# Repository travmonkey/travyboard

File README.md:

# travyboard

## A corne style keyboard with the Pico SDK and TinyUSB

A personal project demonstrating how to build a keyboard using the 
Raspberry Pi Pico microcontroller in c++.

### Requirements

- Two Raspberry Pi Picos
- Cmake and gcc/g++ installed. May want to set up wsl2 on Windows.
- Pico SDK [GitHub Repo](https://github.com/raspberrypi/pico-sdk)

### Setup

1. Clone the Pico SDK and update the submodules
```sh
git clone https://github.com/raspberrypi/pico-sdk.git
cd pico-sdk
git submodule update --init
```

2. Set an environment variable so cmake can find the sdk
```sh
export PICO_SDK_PATH=`<pico sdk path>`
```

3. Clone this repository:
```sh
git clone https://github.com/travmonkey/travyboard.git
cd travyboard
```

4. Create build folder and build the project:
```sh
cd firmware
mkdir build && cd build
cmake -DCMAKE_EXPORT_COMPILE_COMMANDS=ON .. # Export the compile commands for clangd to see
make
```

5. Mount and flash both picos with the master and slave compiled .uf2 code.
```sh
mkdir ~/rpi-pico
sudo fdisk -l # Find the pico device
sudo mount /dev/sdx1 /home/`<user>`/rpi-pico
sudo cp src/master.uf2 /home/`<user>`/rpi-pico/
```
Alternativly you can modify the script I wrote to include your own directories and username

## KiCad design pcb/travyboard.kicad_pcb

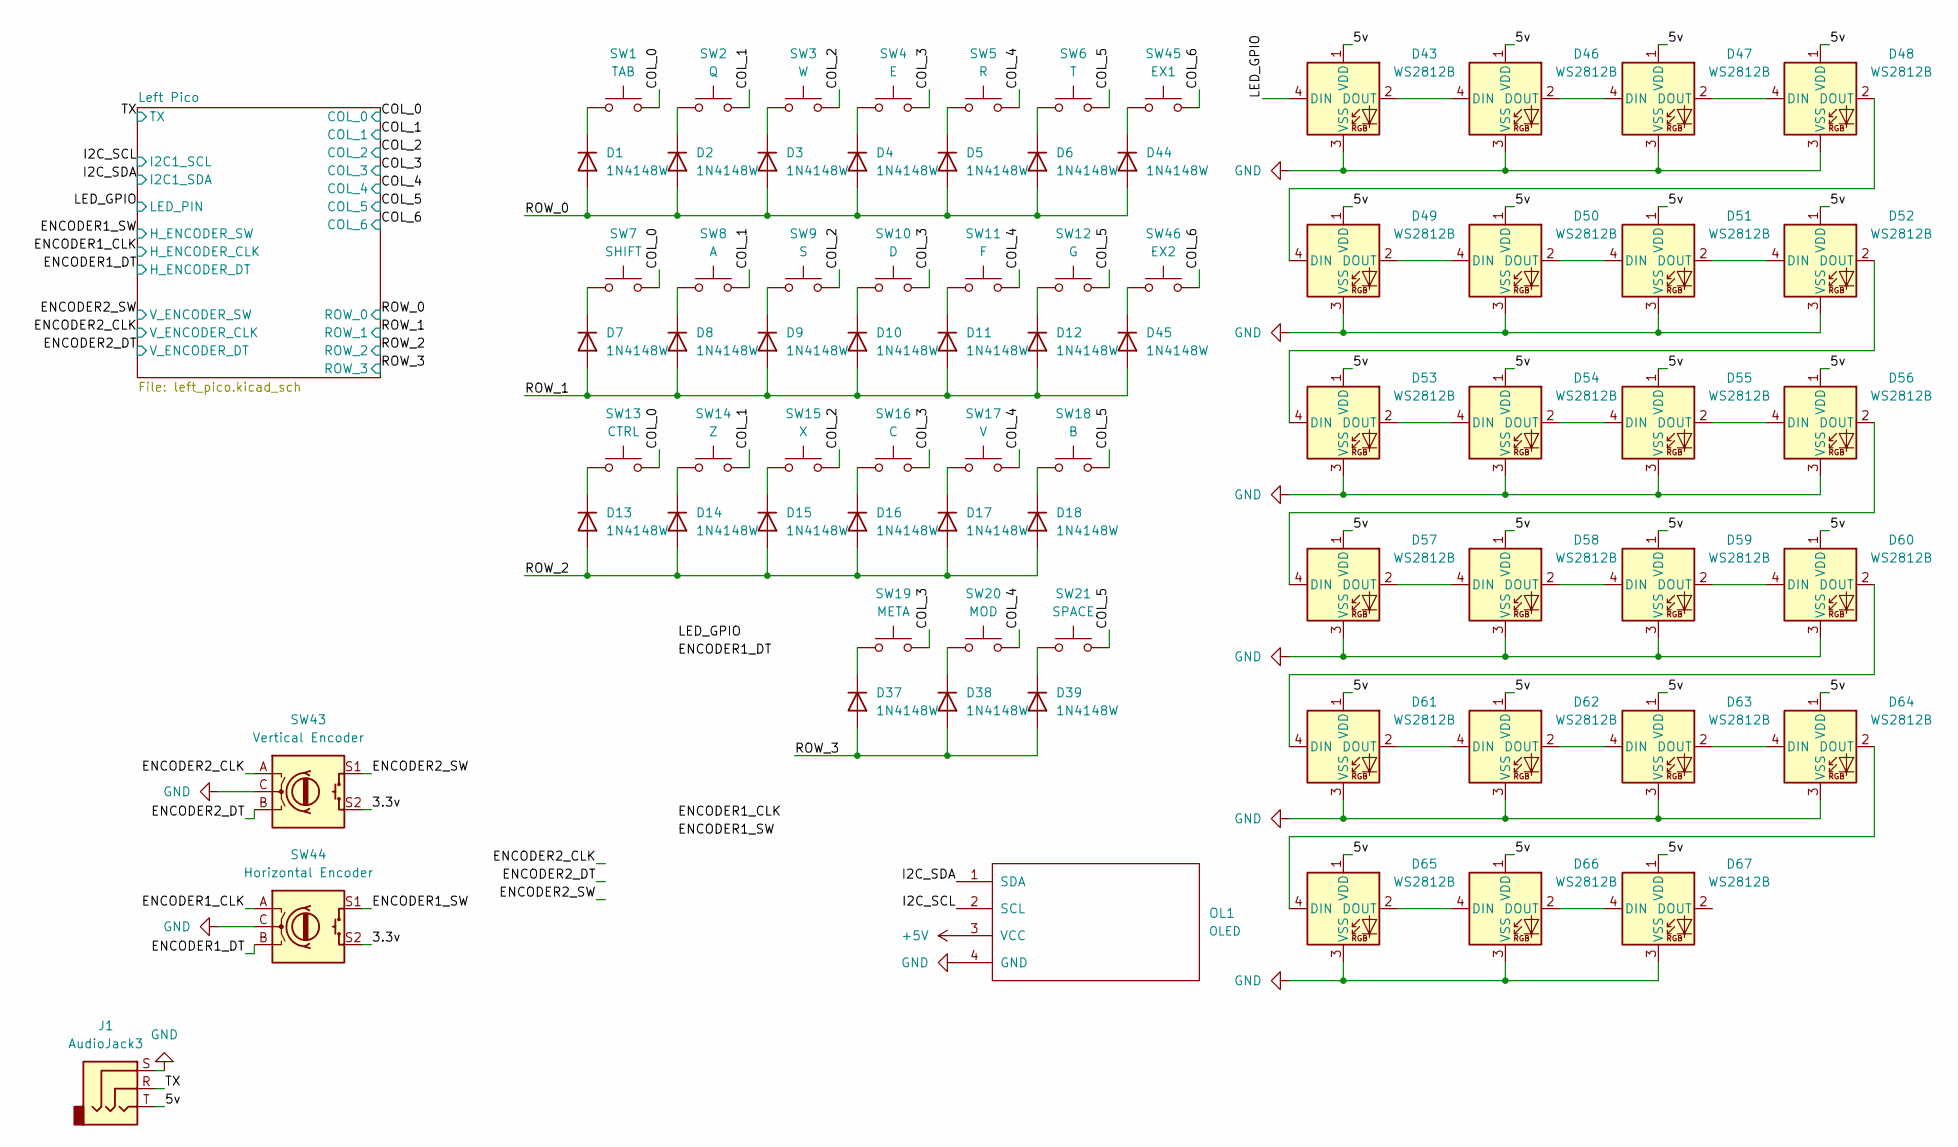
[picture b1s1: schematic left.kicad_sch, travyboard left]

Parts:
D1, D2, D3, D4, D5, D6, D7, D8, D9, D10, D11, D12, D13, D14, D15, D16, D17, D18, D37, D38, D39, D44, D45: 1N4148W; D_SOD-123
D43, D46, D47, D48, D49, D50, D51, D52, D53, D54, D55, D56, D57, D58, D59, D60, D61, D62, D63, D64, D65, D66, D67: WS2812B; LED_WS2812B_PLCC4_5.0x5.0mm_P3.2mm
J1: AudioJack3; PJ-399B-6A
OL1: OLED; SSD1306-0.91-OLED-4pin-128x32
SW1: TAB; CherryMX_Hotswap
SW2: Q; CherryMX_Hotswap
SW3: W; CherryMX_Hotswap
SW4: E; CherryMX_Hotswap
SW5: R; CherryMX_Hotswap
SW6: T; CherryMX_Hotswap
SW7: SHIFT; CherryMX_Hotswap
SW8: A; CherryMX_Hotswap
SW9: S; CherryMX_Hotswap
SW10: D; CherryMX_Hotswap
SW11: F; CherryMX_Hotswap
SW12: G; CherryMX_Hotswap
SW13: CTRL; CherryMX_Hotswap
SW14: Z; CherryMX_Hotswap
SW15: X; CherryMX_Hotswap
SW16: C; CherryMX_Hotswap
SW17: V; CherryMX_Hotswap
SW18: B; CherryMX_Hotswap
SW19: META; CherryMX_Hotswap
SW20: MOD; CherryMX_Hotswap
SW21: SPACE; CherryMX_Hotswap
SW43: Vertical Encoder; PEC12R-4220F-20024
SW44: Horizontal Encoder; PEC12R-2120F-S0012
SW45: EX1; CherryMX_Hotswap
SW46: EX2; CherryMX_Hotswap

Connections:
+5V: OL1.3 (VCC); also elsewhere on the board
/Left Half/3.3v: SW43.S2, SW44.S2
/Left Half/5v: D43.1 (VDD), D46.1 (VDD), D47.1 (VDD), D48.1 (VDD), D49.1 (VDD), D50.1 (VDD), D51.1 (VDD), D52.1 (VDD), D53.1 (VDD), D54.1 (VDD), D55.1 (VDD), D56.1 (VDD), D57.1 (VDD), D58.1 (VDD), D59.1 (VDD), D60.1 (VDD), D61.1 (VDD), D62.1 (VDD), D63.1 (VDD), D64.1 (VDD), D65.1 (VDD), D66.1 (VDD), D67.1 (VDD), J1.T
/Left Half/COL_0: SW1.2, SW7.2, SW13.2; also elsewhere on the board
/Left Half/COL_1: SW2.2, SW8.2, SW14.2; also elsewhere on the board
/Left Half/COL_2: SW3.2, SW9.2, SW15.2; also elsewhere on the board
/Left Half/COL_3: SW4.2, SW10.2, SW16.2, SW19.2; also elsewhere on the board
/Left Half/COL_4: SW5.2, SW11.2, SW17.2, SW20.2; also elsewhere on the board
/Left Half/COL_5: SW6.2, SW12.2, SW18.2, SW21.2; also elsewhere on the board
/Left Half/COL_6: SW45.2, SW46.2; also elsewhere on the board
/Left Half/ENCODER1_CLK: SW44.A; also elsewhere on the board
/Left Half/ENCODER1_DT: SW44.B; also elsewhere on the board
/Left Half/ENCODER1_SW: SW44.S1; also elsewhere on the board
/Left Half/ENCODER2_CLK: SW43.A; also elsewhere on the board
/Left Half/ENCODER2_DT: SW43.B; also elsewhere on the board
/Left Half/ENCODER2_SW: SW43.S1; also elsewhere on the board
/Left Half/I2C_SCL: OL1.2 (SCL); also elsewhere on the board
/Left Half/I2C_SDA: OL1.1 (SDA); also elsewhere on the board
/Left Half/LED_GPIO: D43.4 (DIN); also elsewhere on the board
/Left Half/ROW_0: D1.2 (A), D2.2 (A), D3.2 (A), D4.2 (A), D5.2 (A), D6.2 (A), D44.2 (A); also elsewhere on the board
/Left Half/ROW_1: D7.2 (A), D8.2 (A), D9.2 (A), D10.2 (A), D11.2 (A), D12.2 (A), D45.2 (A); also elsewhere on the board
/Left Half/ROW_2: D13.2 (A), D14.2 (A), D15.2 (A), D16.2 (A), D17.2 (A), D18.2 (A); also elsewhere on the board
/Left Half/ROW_3: D37.2 (A), D38.2 (A), D39.2 (A); also elsewhere on the board
/Left Half/TX: J1.R; also elsewhere on the board
GND: D43.3 (VSS), D46.3 (VSS), D47.3 (VSS), D48.3 (VSS), D49.3 (VSS), D50.3 (VSS), D51.3 (VSS), D52.3 (VSS), D53.3 (VSS), D54.3 (VSS), D55.3 (VSS), D56.3 (VSS), D57.3 (VSS), D58.3 (VSS), D59.3 (VSS), D60.3 (VSS), D61.3 (VSS), D62.3 (VSS), D63.3 (VSS), D64.3 (VSS), D65.3 (VSS), D66.3 (VSS), D67.3 (VSS), J1.S, OL1.4 (GND), SW43.C, SW44.C; also elsewhere on the board
unnamed: D1.1 (K), SW1.1
unnamed: D2.1 (K), SW2.1
unnamed: D3.1 (K), SW3.1
unnamed: D4.1 (K), SW4.1
unnamed: D5.1 (K), SW5.1
unnamed: D6.1 (K), SW6.1
unnamed: D7.1 (K), SW7.1
unnamed: D8.1 (K), SW8.1
unnamed: D9.1 (K), SW9.1
unnamed: D10.1 (K), SW10.1
unnamed: D11.1 (K), SW11.1
unnamed: D12.1 (K), SW12.1
unnamed: D13.1 (K), SW13.1
unnamed: D14.1 (K), SW14.1
unnamed: D15.1 (K), SW15.1
unnamed: D16.1 (K), SW16.1
unnamed: D17.1 (K), SW17.1
unnamed: D18.1 (K), SW18.1
unnamed: D37.1 (K), SW19.1
unnamed: D38.1 (K), SW20.1
unnamed: D39.1 (K), SW21.1
unnamed: D43.2 (DOUT), D46.4 (DIN)
unnamed: D44.1 (K), SW45.1
unnamed: D45.1 (K), SW46.1
unnamed: D46.2 (DOUT), D47.4 (DIN)
unnamed: D47.2 (DOUT), D48.4 (DIN)
unnamed: D48.2 (DOUT), D49.4 (DIN)
unnamed: D49.2 (DOUT), D50.4 (DIN)
unnamed: D50.2 (DOUT), D51.4 (DIN)
unnamed: D51.2 (DOUT), D52.4 (DIN)
unnamed: D52.2 (DOUT), D53.4 (DIN)
unnamed: D53.2 (DOUT), D54.4 (DIN)
unnamed: D54.2 (DOUT), D55.4 (DIN)
unnamed: D55.2 (DOUT), D56.4 (DIN)
unnamed: D56.2 (DOUT), D57.4 (DIN)
unnamed: D57.2 (DOUT), D58.4 (DIN)
unnamed: D58.2 (DOUT), D59.4 (DIN)
unnamed: D59.2 (DOUT), D60.4 (DIN)
unnamed: D60.2 (DOUT), D61.4 (DIN)
unnamed: D61.2 (DOUT), D62.4 (DIN)
unnamed: D62.2 (DOUT), D63.4 (DIN)
unnamed: D63.2 (DOUT), D64.4 (DIN)
unnamed: D64.2 (DOUT), D65.4 (DIN)
unnamed: D65.2 (DOUT), D66.4 (DIN)
unnamed: D66.2 (DOUT), D67.4 (DIN)

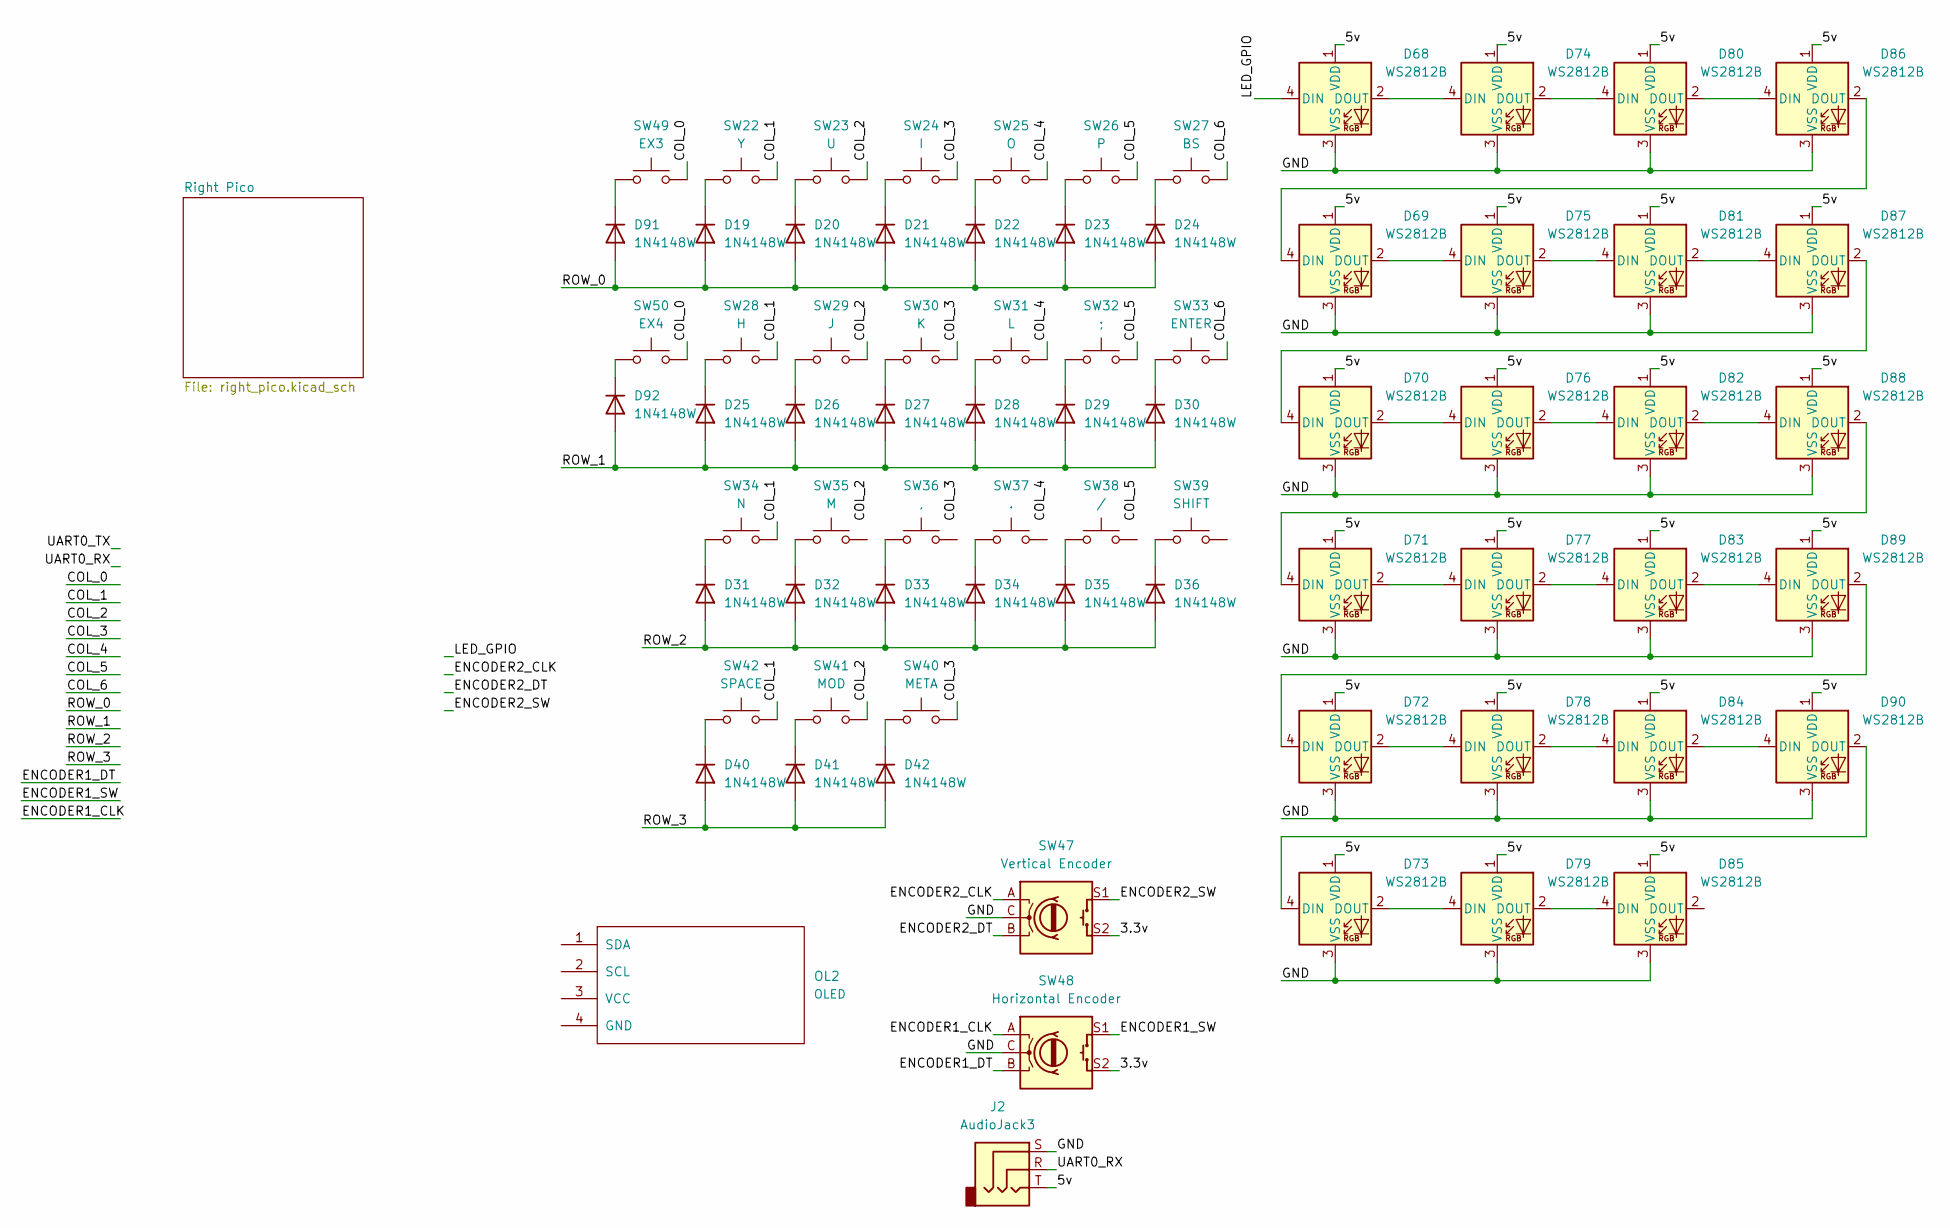
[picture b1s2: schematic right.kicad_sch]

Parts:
D19, D20, D21, D22, D23, D24, D25, D26, D27, D28, D29, D30, D31, D32, D33, D34, D35, D36, D40, D41, D42, D91, D92: 1N4148W; D_SOD-123
D68, D69, D70, D71, D72, D73, D74, D75, D76, D77, D78, D79, D80, D81, D82, D83, D84, D85, D86, D87, D88, D89, D90: WS2812B; LED_WS2812B_PLCC4_5.0x5.0mm_P3.2mm
J2: AudioJack3; PJ-399B-6A
OL2: OLED; SSD1306-0.91-OLED-4pin-128x32
SW22: Y; CherryMX_Hotswap
SW23: U; CherryMX_Hotswap
SW24: I; CherryMX_Hotswap
SW25: O; CherryMX_Hotswap
SW26: P; CherryMX_Hotswap
SW27: BS; CherryMX_Hotswap
SW28: H; CherryMX_Hotswap
SW29: J; CherryMX_Hotswap
SW30: K; CherryMX_Hotswap
SW31: L; CherryMX_Hotswap
SW32: ;; CherryMX_Hotswap
SW33: ENTER; CherryMX_Hotswap
SW34: N; CherryMX_Hotswap
SW35: M; CherryMX_Hotswap
SW36: ,; CherryMX_Hotswap
SW37: .; CherryMX_Hotswap
SW38: /; CherryMX_Hotswap
SW39: SHIFT; CherryMX_Hotswap
SW40: META; CherryMX_Hotswap
SW41: MOD; CherryMX_Hotswap
SW42: SPACE; CherryMX_Hotswap
SW47: Vertical Encoder; PEC12R-4220F-20024
SW48: Horizontal Encoder; PEC12R-2120F-S0012
SW49: EX3; CherryMX_Hotswap
SW50: EX4; CherryMX_Hotswap

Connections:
/Right Half/3.3v: SW47.S2, SW48.S2
/Right Half/5v: D68.1 (VDD), D69.1 (VDD), D70.1 (VDD), D71.1 (VDD), D72.1 (VDD), D73.1 (VDD), D74.1 (VDD), D75.1 (VDD), D76.1 (VDD), D77.1 (VDD), D78.1 (VDD), D79.1 (VDD), D80.1 (VDD), D81.1 (VDD), D82.1 (VDD), D83.1 (VDD), D84.1 (VDD), D85.1 (VDD), D86.1 (VDD), D87.1 (VDD), D88.1 (VDD), D89.1 (VDD), D90.1 (VDD), J2.T
/Right Half/COL_0: SW49.2, SW50.2
/Right Half/COL_1: SW22.2, SW28.2, SW34.2, SW42.2
/Right Half/COL_2: SW23.2, SW29.2, SW41.2
/Right Half/COL_3: SW24.2, SW30.2, SW40.2
/Right Half/COL_4: SW25.2, SW31.2
/Right Half/COL_5: SW26.2, SW32.2
/Right Half/COL_6: SW27.2, SW33.2
/Right Half/ENCODER1_CLK: SW48.A
/Right Half/ENCODER1_DT: SW48.B
/Right Half/ENCODER1_SW: SW48.S1
/Right Half/ENCODER2_CLK: SW47.A
/Right Half/ENCODER2_DT: SW47.B
/Right Half/ENCODER2_SW: SW47.S1
/Right Half/GND: D68.3 (VSS), D69.3 (VSS), D70.3 (VSS), D71.3 (VSS), D72.3 (VSS), D73.3 (VSS), D74.3 (VSS), D75.3 (VSS), D76.3 (VSS), D77.3 (VSS), D78.3 (VSS), D79.3 (VSS), D80.3 (VSS), D81.3 (VSS), D82.3 (VSS), D83.3 (VSS), D84.3 (VSS), D85.3 (VSS), D86.3 (VSS), D87.3 (VSS), D88.3 (VSS), D89.3 (VSS), D90.3 (VSS), J2.S, SW47.C, SW48.C
/Right Half/LED_GPIO: D68.4 (DIN)
/Right Half/ROW_0: D19.2 (A), D20.2 (A), D21.2 (A), D22.2 (A), D23.2 (A), D24.2 (A), D91.2 (A)
/Right Half/ROW_1: D25.2 (A), D26.2 (A), D27.2 (A), D28.2 (A), D29.2 (A), D30.2 (A), D92.2 (A)
/Right Half/ROW_2: D31.2 (A), D32.2 (A), D33.2 (A), D34.2 (A), D35.2 (A), D36.2 (A)
/Right Half/ROW_3: D40.2 (A), D41.2 (A), D42.2 (A)
/Right Half/UART0_RX: J2.R
unnamed: D19.1 (K), SW22.1
unnamed: D20.1 (K), SW23.1
unnamed: D21.1 (K), SW24.1
unnamed: D22.1 (K), SW25.1
unnamed: D23.1 (K), SW26.1
unnamed: D24.1 (K), SW27.1
unnamed: D25.1 (K), SW28.1
unnamed: D26.1 (K), SW29.1
unnamed: D27.1 (K), SW30.1
unnamed: D28.1 (K), SW31.1
unnamed: D29.1 (K), SW32.1
unnamed: D30.1 (K), SW33.1
unnamed: D31.1 (K), SW34.1
unnamed: D32.1 (K), SW35.1
unnamed: D33.1 (K), SW36.1
unnamed: D34.1 (K), SW37.1
unnamed: D35.1 (K), SW38.1
unnamed: D36.1 (K), SW39.1
unnamed: D40.1 (K), SW42.1
unnamed: D41.1 (K), SW41.1
unnamed: D42.1 (K), SW40.1
unnamed: D68.2 (DOUT), D74.4 (DIN)
unnamed: D69.4 (DIN), D86.2 (DOUT)
unnamed: D69.2 (DOUT), D75.4 (DIN)
unnamed: D70.4 (DIN), D87.2 (DOUT)
unnamed: D70.2 (DOUT), D76.4 (DIN)
unnamed: D71.4 (DIN), D88.2 (DOUT)
unnamed: D71.2 (DOUT), D77.4 (DIN)
unnamed: D72.4 (DIN), D89.2 (DOUT)
unnamed: D72.2 (DOUT), D78.4 (DIN)
unnamed: D73.4 (DIN), D90.2 (DOUT)
unnamed: D73.2 (DOUT), D79.4 (DIN)
unnamed: D74.2 (DOUT), D80.4 (DIN)
unnamed: D75.2 (DOUT), D81.4 (DIN)
unnamed: D76.2 (DOUT), D82.4 (DIN)
unnamed: D77.2 (DOUT), D83.4 (DIN)
unnamed: D78.2 (DOUT), D84.4 (DIN)
unnamed: D79.2 (DOUT), D85.4 (DIN)
unnamed: D80.2 (DOUT), D86.4 (DIN)
unnamed: D81.2 (DOUT), D87.4 (DIN)
unnamed: D82.2 (DOUT), D88.4 (DIN)
unnamed: D83.2 (DOUT), D89.4 (DIN)
unnamed: D84.2 (DOUT), D90.4 (DIN)
unnamed: D91.1 (K), SW49.1
unnamed: D92.1 (K), SW50.1

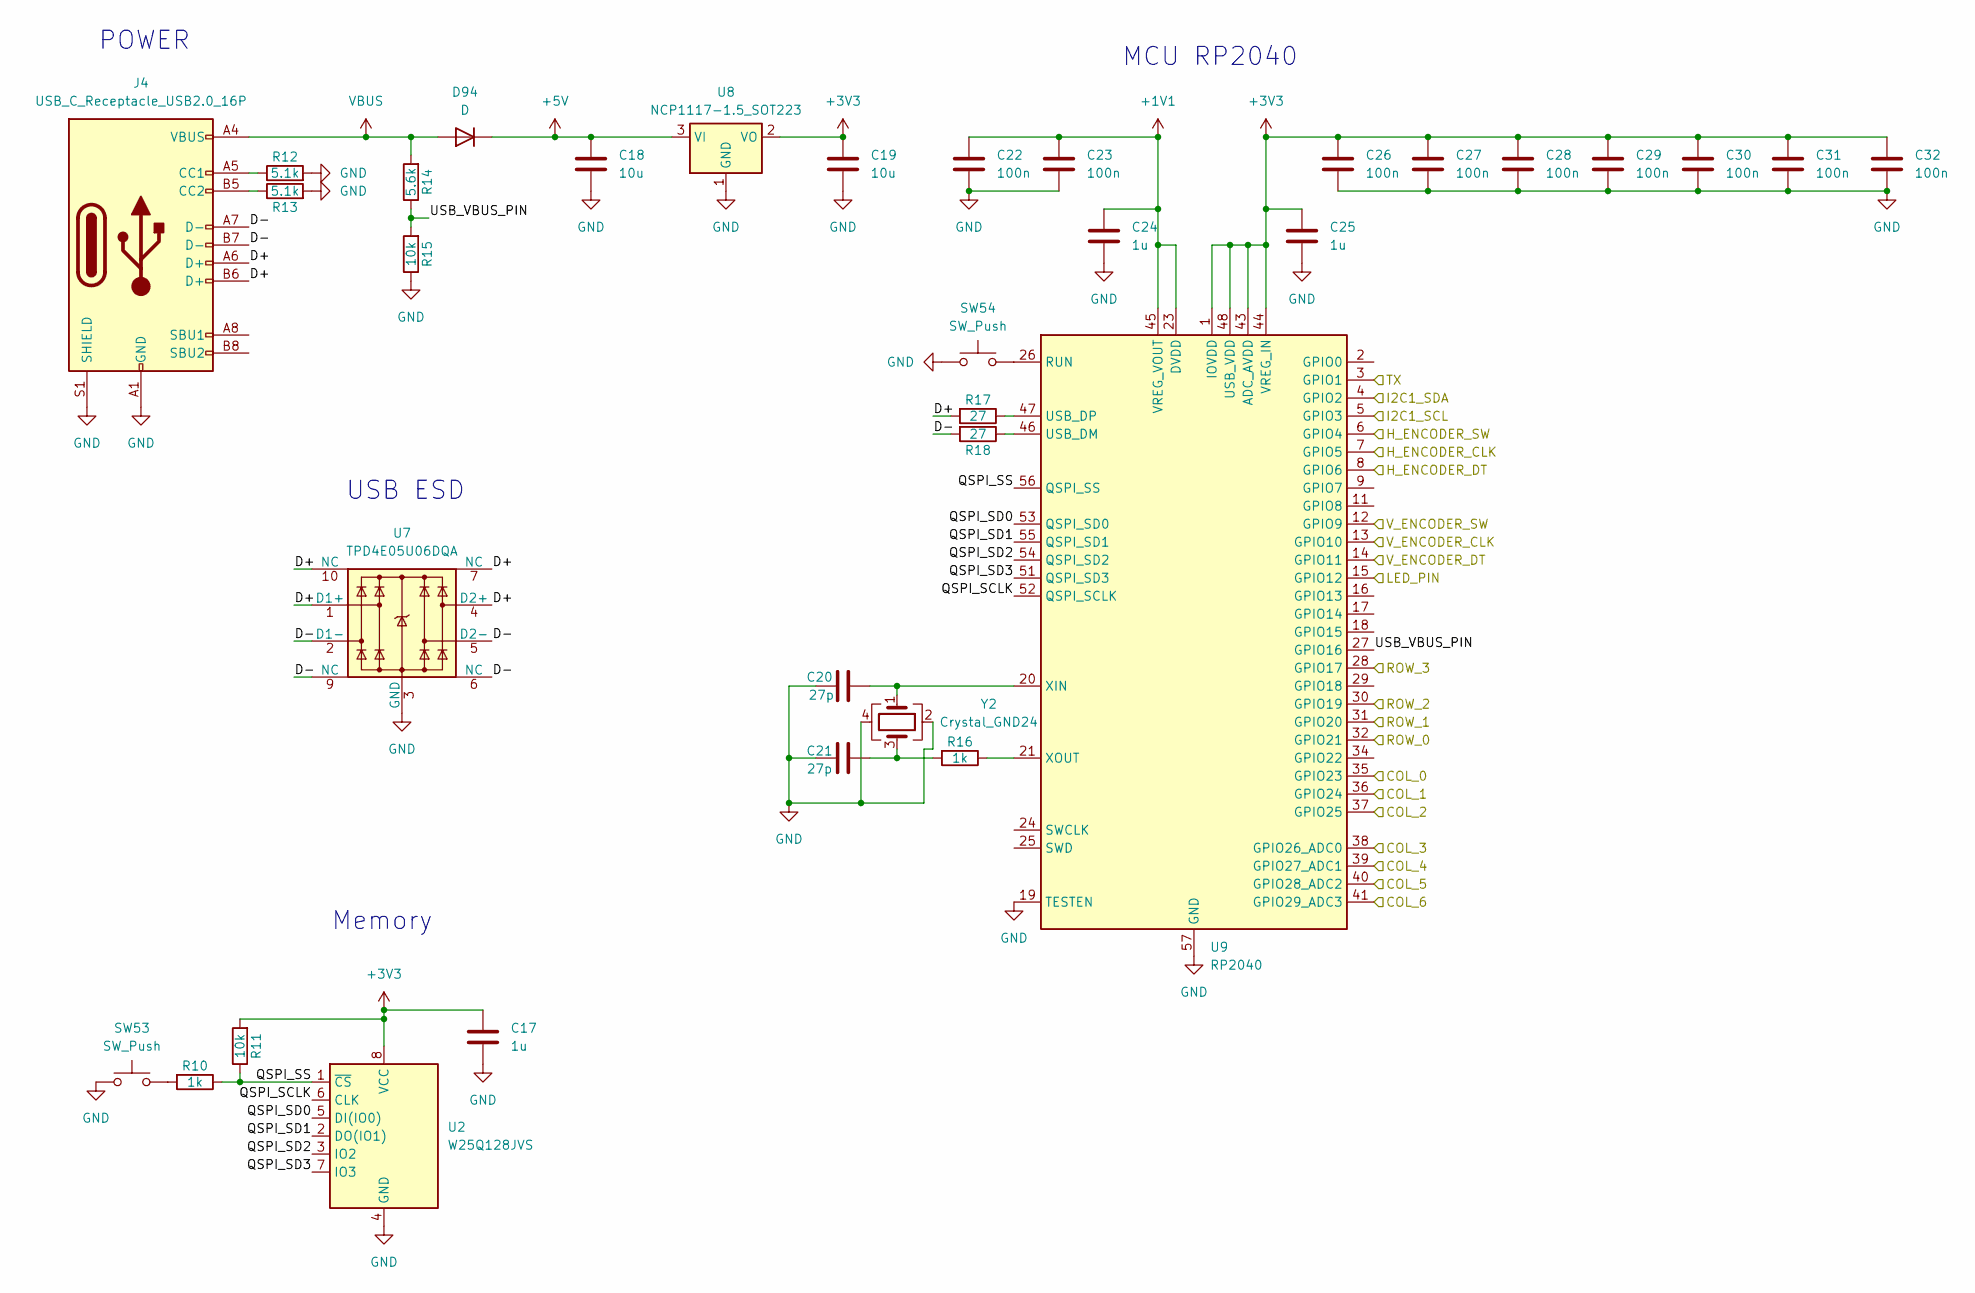
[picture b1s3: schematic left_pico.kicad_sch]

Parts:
C17, C24, C25: 1u; C_0402_1005Metric
C18, C19: 10u; C_0402_1005Metric
C20, C21: 27p; C_0402_1005Metric
C22, C23, C26, C27, C28, C29, C30, C31, C32: 100n; C_0402_1005Metric
D94: D; D_SOD-523
J4: USB_C_Receptacle_USB2.0_16P; TYPE-C-31-M-13C
R10, R16: 1k; R_0402_1005Metric
R11, R15: 10k; R_0402_1005Metric
R12, R13: 5.1k; R_0402_1005Metric
R14: 5.6k; R_0402_1005Metric
R17, R18: 27; R_0402_1005Metric
SW53, SW54: SW_Push
U2: W25Q128JVS; SOIC-8_5.23x5.23mm_P1.27mm
U7: TPD4E05U06DQA; USON-10_2.5x1.0mm_P0.5mm
U8: NCP1117-1.5_SOT223; SOT-223-3_TabPin2
U9: RP2040; QFN-56-1EP_7x7mm_P0.4mm_EP3.2x3.2mm
Y2: Crystal_GND24; Crystal_SMD_3225-4Pin_3.2x2.5mm

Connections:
+1V1: C22.1, C23.1, C24.1, U9.23 (DVDD), U9.45 (VREG_VOUT), U9.50 (DVDD); also elsewhere on the board
+3V3: C17.1, C19.1, C25.1, C26.1, C27.1, C28.1, C29.1, C30.1, C31.1, C32.1, R11.2, U2.8 (VCC), U8.2 (VO), U9.1 (IOVDD), U9.10 (IOVDD), U9.22 (IOVDD), U9.33 (IOVDD), U9.42 (IOVDD), U9.43 (ADC_AVDD), U9.44 (VREG_IN), U9.48 (USB_VDD), U9.49 (IOVDD); also elsewhere on the board
+5V: C18.1, D94.1 (K), U8.3 (VI); also elsewhere on the board
/Left Half/COL_0: U9.35 (GPIO23); also elsewhere on the board
/Left Half/COL_1: U9.36 (GPIO24); also elsewhere on the board
/Left Half/COL_2: U9.37 (GPIO25); also elsewhere on the board
/Left Half/COL_3: U9.38 (GPIO26_ADC0); also elsewhere on the board
/Left Half/COL_4: U9.39 (GPIO27_ADC1); also elsewhere on the board
/Left Half/COL_5: U9.40 (GPIO28_ADC2); also elsewhere on the board
/Left Half/COL_6: U9.41 (GPIO29_ADC3); also elsewhere on the board
/Left Half/ENCODER1_CLK: U9.7 (GPIO5); also elsewhere on the board
/Left Half/ENCODER1_DT: U9.8 (GPIO6); also elsewhere on the board
/Left Half/ENCODER1_SW: U9.6 (GPIO4); also elsewhere on the board
/Left Half/ENCODER2_CLK: U9.13 (GPIO10); also elsewhere on the board
/Left Half/ENCODER2_DT: U9.14 (GPIO11); also elsewhere on the board
/Left Half/ENCODER2_SW: U9.12 (GPIO9); also elsewhere on the board
/Left Half/I2C_SCL: U9.5 (GPIO3); also elsewhere on the board
/Left Half/I2C_SDA: U9.4 (GPIO2); also elsewhere on the board
/Left Half/LED_GPIO: U9.15 (GPIO12); also elsewhere on the board
/Left Half/Left Pico/D+: J4.A6 (D+), J4.B6 (D+), R17.2, U7.1 (D1+), U7.4 (D2+), U7.7 (NC), U7.10 (NC)
/Left Half/Left Pico/D-: J4.A7 (D-), J4.B7 (D-), R18.2, U7.2 (D1-), U7.5 (D2-), U7.6 (NC), U7.9 (NC)
/Left Half/Left Pico/QSPI_SCLK: U2.6 (CLK), U9.52 (QSPI_SCLK)
/Left Half/Left Pico/QSPI_SD0: U2.5 (DI(IO0)), U9.53 (QSPI_SD0)
/Left Half/Left Pico/QSPI_SD1: U2.2 (DO(IO1)), U9.55 (QSPI_SD1)
/Left Half/Left Pico/QSPI_SD2: U2.3 (IO2), U9.54 (QSPI_SD2)
/Left Half/Left Pico/QSPI_SD3: U2.7 (IO3), U9.51 (QSPI_SD3)
/Left Half/Left Pico/QSPI_SS: R10.1, R11.1, U2.1 (~CS), U9.56 (QSPI_SS)
/Left Half/Left Pico/USB_VBUS_PIN: R14.1, R15.2, U9.27 (GPIO16)
/Left Half/ROW_0: U9.32 (GPIO21); also elsewhere on the board
/Left Half/ROW_1: U9.31 (GPIO20); also elsewhere on the board
/Left Half/ROW_2: U9.30 (GPIO19); also elsewhere on the board
/Left Half/ROW_3: U9.28 (GPIO17); also elsewhere on the board
/Left Half/TX: U9.3 (GPIO1); also elsewhere on the board
GND: C17.2, C18.2, C19.2, C20.1, C21.1, C22.2, C23.2, C24.2, C25.2, C26.2, C27.2, C28.2, C29.2, C30.2, C31.2, C32.2, J4.A1 (GND), J4.A12 (GND), J4.B1 (GND), J4.B12 (GND), J4.S1 (SHIELD), R12.2, R13.2, R15.1, SW53.1, SW54.1, U2.4 (GND), U7.3 (GND), U7.8 (GND), U8.1 (GND), U9.19 (TESTEN), U9.57 (GND), Y2.2, Y2.4; also elsewhere on the board
unnamed: C21.2, R16.2, Y2.3
unnamed: J4.A5 (CC1), R12.1
unnamed: J4.B5 (CC2), R13.1
unnamed: R10.2, SW53.2
unnamed: SW54.2, U9.26 (RUN)
unnamed: R18.1, U9.46 (USB_DM)
unnamed: R17.1, U9.47 (USB_DP)
unnamed: C20.2, U9.20 (XIN), Y2.1
unnamed: R16.1, U9.21 (XOUT)
VBUS: D94.2 (A), J4.A4 (VBUS), J4.A9 (VBUS), J4.B4 (VBUS), J4.B9 (VBUS), R14.2; also elsewhere on the board

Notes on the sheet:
USB ESD
MCU RP2040
POWER
Memory

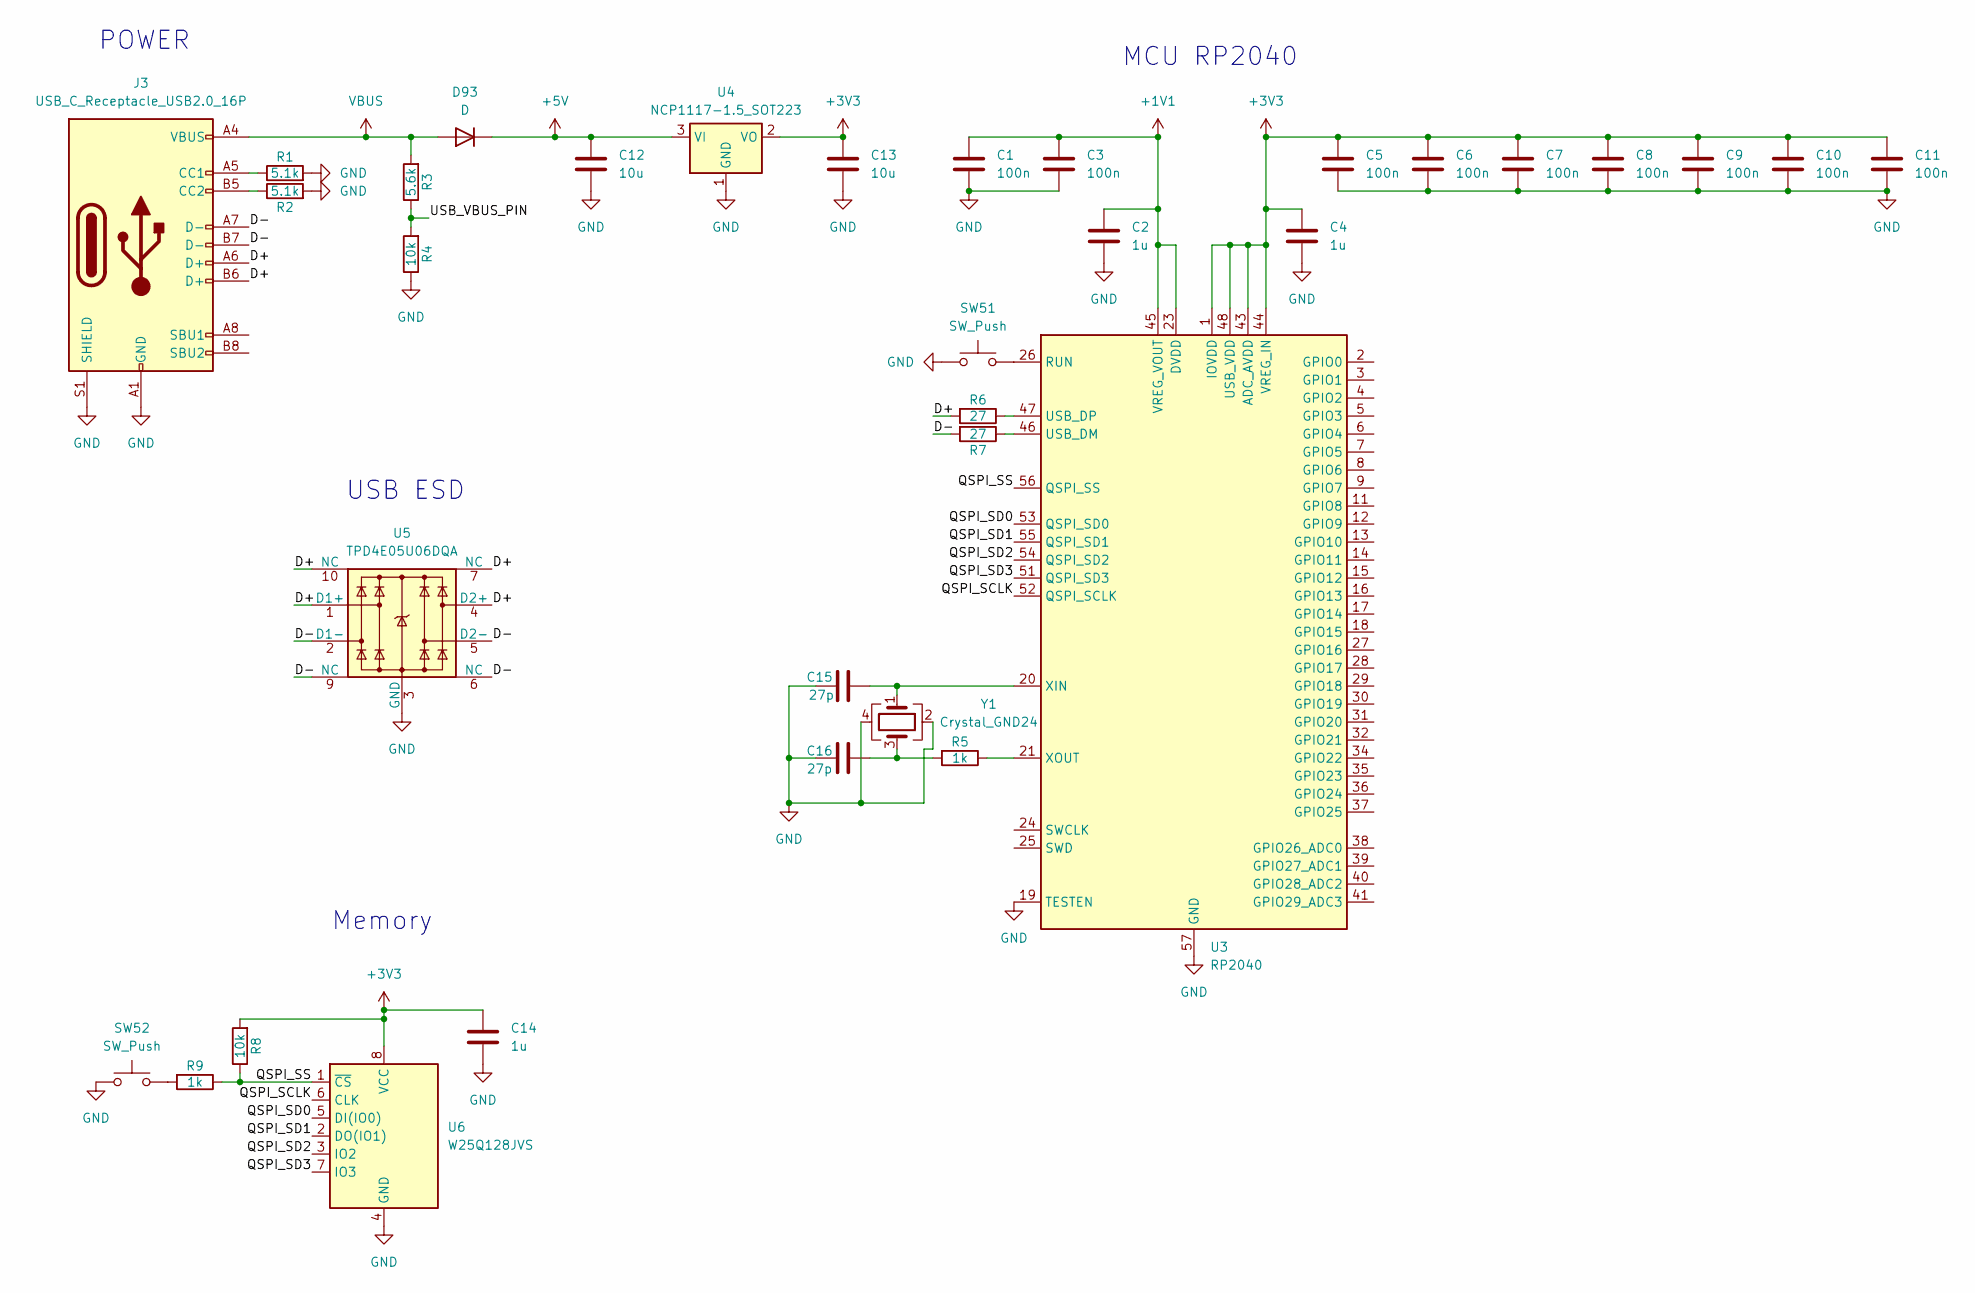
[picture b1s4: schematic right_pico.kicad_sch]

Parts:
C1, C3, C5, C6, C7, C8, C9, C10, C11: 100n; C_0402_1005Metric
C2, C4, C14: 1u; C_0402_1005Metric
C12, C13: 10u; C_0402_1005Metric
C15, C16: 27p; C_0402_1005Metric
D93: D; D_SOD-523
J3: USB_C_Receptacle_USB2.0_16P; TYPE-C-31-M-13C
R1, R2: 5.1k; R_0402_1005Metric
R3: 5.6k; R_0402_1005Metric
R4, R8: 10k; R_0402_1005Metric
R5, R9: 1k; R_0402_1005Metric
R6, R7: 27; R_0402_1005Metric
SW51, SW52: SW_Push
U3: RP2040; QFN-56-1EP_7x7mm_P0.4mm_EP3.2x3.2mm
U4: NCP1117-1.5_SOT223; SOT-223-3_TabPin2
U5: TPD4E05U06DQA; USON-10_2.5x1.0mm_P0.5mm
U6: W25Q128JVS; SOIC-8_5.23x5.23mm_P1.27mm
Y1: Crystal_GND24; Crystal_SMD_3225-4Pin_3.2x2.5mm

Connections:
+1V1: C1.1, C2.1, C3.1, U3.23 (DVDD), U3.45 (VREG_VOUT), U3.50 (DVDD); also elsewhere on the board
+3V3: C4.1, C5.1, C6.1, C7.1, C8.1, C9.1, C10.1, C11.1, C13.1, C14.1, R8.2, U3.1 (IOVDD), U3.10 (IOVDD), U3.22 (IOVDD), U3.33 (IOVDD), U3.42 (IOVDD), U3.43 (ADC_AVDD), U3.44 (VREG_IN), U3.48 (USB_VDD), U3.49 (IOVDD), U4.2 (VO), U6.8 (VCC); also elsewhere on the board
+5V: C12.1, D93.1 (K), U4.3 (VI); also elsewhere on the board
/Right Half/Right Pico/D+: J3.A6 (D+), J3.B6 (D+), R6.2, U5.1 (D1+), U5.4 (D2+), U5.7 (NC), U5.10 (NC)
/Right Half/Right Pico/D-: J3.A7 (D-), J3.B7 (D-), R7.2, U5.2 (D1-), U5.5 (D2-), U5.6 (NC), U5.9 (NC)
/Right Half/Right Pico/QSPI_SCLK: U3.52 (QSPI_SCLK), U6.6 (CLK)
/Right Half/Right Pico/QSPI_SD0: U3.53 (QSPI_SD0), U6.5 (DI(IO0))
/Right Half/Right Pico/QSPI_SD1: U3.55 (QSPI_SD1), U6.2 (DO(IO1))
/Right Half/Right Pico/QSPI_SD2: U3.54 (QSPI_SD2), U6.3 (IO2)
/Right Half/Right Pico/QSPI_SD3: U3.51 (QSPI_SD3), U6.7 (IO3)
/Right Half/Right Pico/QSPI_SS: R8.1, R9.1, U3.56 (QSPI_SS), U6.1 (~CS)
/Right Half/Right Pico/USB_VBUS_PIN: R3.1, R4.2
GND: C1.2, C2.2, C3.2, C4.2, C5.2, C6.2, C7.2, C8.2, C9.2, C10.2, C11.2, C12.2, C13.2, C14.2, C15.1, C16.1, J3.A1 (GND), J3.A12 (GND), J3.B1 (GND), J3.B12 (GND), J3.S1 (SHIELD), R1.2, R2.2, R4.1, SW51.1, SW52.1, U3.19 (TESTEN), U3.57 (GND), U4.1 (GND), U5.3 (GND), U5.8 (GND), U6.4 (GND), Y1.2, Y1.4; also elsewhere on the board
unnamed: C16.2, R5.2, Y1.3
unnamed: J3.A5 (CC1), R1.1
unnamed: J3.B5 (CC2), R2.1
unnamed: R9.2, SW52.2
unnamed: SW51.2, U3.26 (RUN)
unnamed: R7.1, U3.46 (USB_DM)
unnamed: R6.1, U3.47 (USB_DP)
unnamed: C15.2, U3.20 (XIN), Y1.1
unnamed: R5.1, U3.21 (XOUT)
VBUS: D93.2 (A), J3.A4 (VBUS), J3.A9 (VBUS), J3.B4 (VBUS), J3.B9 (VBUS), R3.2; also elsewhere on the board

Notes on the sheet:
POWER
USB ESD
Memory
MCU RP2040

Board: 2 copper layers, 210 parts (125 on the bottom side), 164 nets, no tracks yet.

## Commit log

2024-06-07 Initialize pico environment
2024-06-07 Base working keyboard firmware
2024-06-08 Update gitignore
2024-06-08 Code formatting
2024-06-08 Remove .cache directory
2024-06-08 Add .cache to .gitignore
2024-06-08 Remove clang cache
2024-06-08 Remove .cache for real this time
2024-06-09 Create diode matrix
2024-06-09 Update flash script
2024-06-09 Change dedicated c++ headers to .hpp
2024-06-09 Change project name in CMakeLists.txt
2024-06-09 Change header to .h
2024-06-09 Update flashing script to support master and slave
2024-06-09 Split project into subdirectories
2024-06-09 Enable rotary encoder support
2024-06-09 Move encoder to namespace and create header
2024-06-09 Move .h to .hpp last time for real
2024-06-09 Fix include issues
2024-06-09 Add exit on failed make
2024-06-09 Add README.md
2024-06-09 Change inline code to sh from bash
2024-06-12 Add initial circuit board design
2024-06-12 Add jack 3d model
2024-06-12 Wire left half of pcb
2024-06-12 Move rotary encoder to class
2024-06-13 Add keymap code and basic uart functionality
2024-06-13 Unworking basic oled code
2024-06-13 Rewire left half
2024-06-13 Create base keymap
2024-06-16 Move row and column scanning to loops
2024-06-16 Move .gitignore
2024-06-16 Move row and column to start with 0 on schematic
2024-06-16 Full layer implementation
2024-06-17 Complete layer and key recognition
2024-06-17 Add basic uart keysending functionality
2024-06-18 Make Uart send keypresses
2024-06-18 Update pcb
2024-06-18 Remove old file keyboard.hpp
2024-06-18 Fully functional UART key transmission
2024-06-19 Move if statement inside for loop
2024-06-19 Add more comments and move code around
2024-06-19 Finish initial keymap
2024-06-19 Move uart handling to own function
2024-06-19 Finish fully functional keyboard with layers
2024-06-19 Increase polling rate to 1ms
2024-06-22 Switch to RP2040 chip on board
2024-06-26 Make send_kepress function more descriptive
2024-06-26 Implement basic mouse functionality
2024-08-28 Mouse and encoder testing
2024-08-28 Various changes
2024-10-04 Ignore .ccls-cache
2024-10-04 Fix comparing string with int
2024-10-04 Add picotool
2024-10-04 Change schebang line to environment bash
2024-10-04 Implement debouncing on rotary encoder
2024-10-06 Include shell.nix in repo
2024-10-06 Change declaration for board.h
